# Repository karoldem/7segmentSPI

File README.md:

# 7segmentSPI
Easy 7 segment driver working on SPI. If placed one next to another respective pins are placed next to one another.

This project has never been made before, so make sure, that everything is OK.

Caution: do not print any names, because it's tihgt here, so they are placed randomly.

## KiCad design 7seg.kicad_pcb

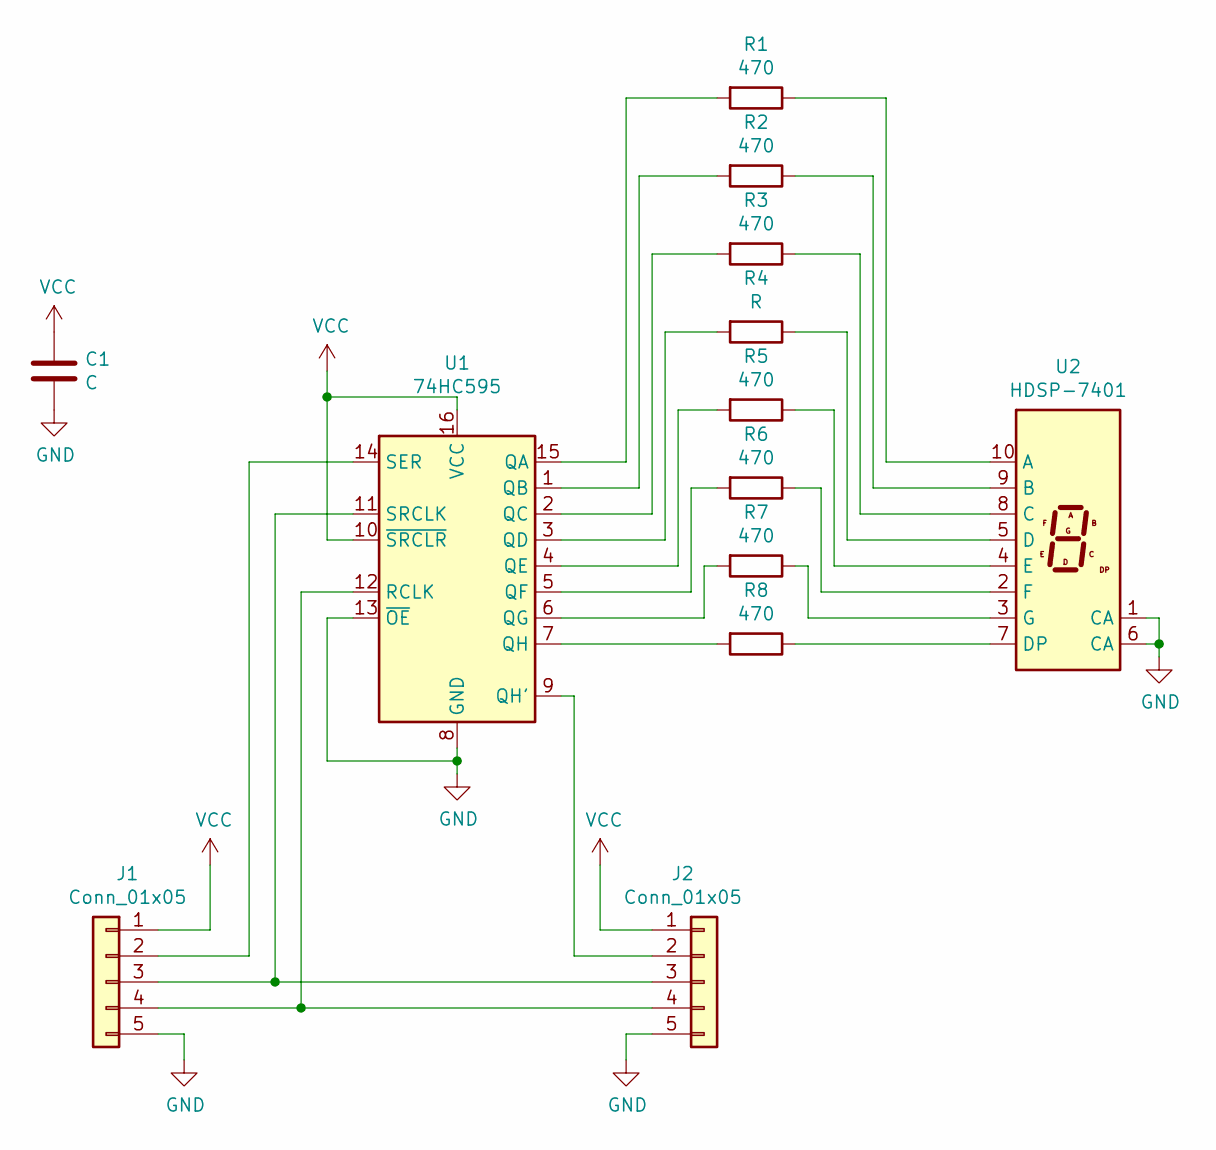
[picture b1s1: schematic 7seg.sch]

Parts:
C1: C; C_0402
J1, J2: Conn_01x05; PinHeader_1x05_P2.54mm_Vertical
R1, R2, R3, R5, R6, R7, R8: 470; R_0201
R4: R; R_0201
U1: 74HC595; TSSOP-16-1EP_4.4x5mm_Pitch0.65mm
U2: HDSP-7401; 7SegmentLED_LTS6760_LTS6780

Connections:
GND: C1.2, J1.5, J2.5, U1.8 (GND), U1.13 (~OE), U2.1 (CA), U2.6 (CA)
unnamed: J1.2, U1.14 (SER)
unnamed: J1.3, J2.3, U1.11 (SRCLK)
unnamed: J1.4, J2.4, U1.12 (RCLK)
unnamed: J2.2, U1.9 (QH')
unnamed: R1.1, U2.10 (A)
unnamed: R1.2, U1.15 (QA)
unnamed: R2.1, U2.9 (B)
unnamed: R2.2, U1.1 (QB)
unnamed: R3.1, U2.8 (C)
unnamed: R3.2, U1.2 (QC)
unnamed: R4.1, U2.5 (D)
unnamed: R4.2, U1.3 (QD)
unnamed: R5.1, U2.4 (E)
unnamed: R5.2, U1.4 (QE)
unnamed: R6.1, U2.2 (F)
unnamed: R6.2, U1.5 (QF)
unnamed: R7.1, U2.3 (G)
unnamed: R7.2, U1.6 (QG)
unnamed: R8.1, U2.7 (DP)
unnamed: R8.2, U1.7 (QH)
VCC: C1.1, J1.1, J2.1, U1.10 (~SRCLR), U1.16 (VCC)

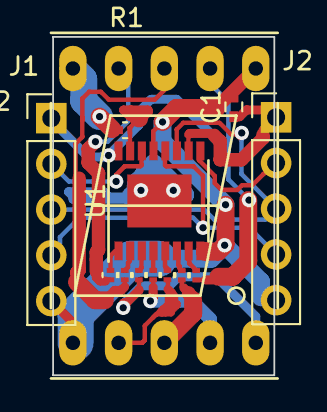
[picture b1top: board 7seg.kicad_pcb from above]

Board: 2 copper layers, 12.3 x 18.8 mm, 13 parts (0 on the bottom side), 22 nets.

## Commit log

2022-02-13 Utworzono za pomocą Colaboratory
